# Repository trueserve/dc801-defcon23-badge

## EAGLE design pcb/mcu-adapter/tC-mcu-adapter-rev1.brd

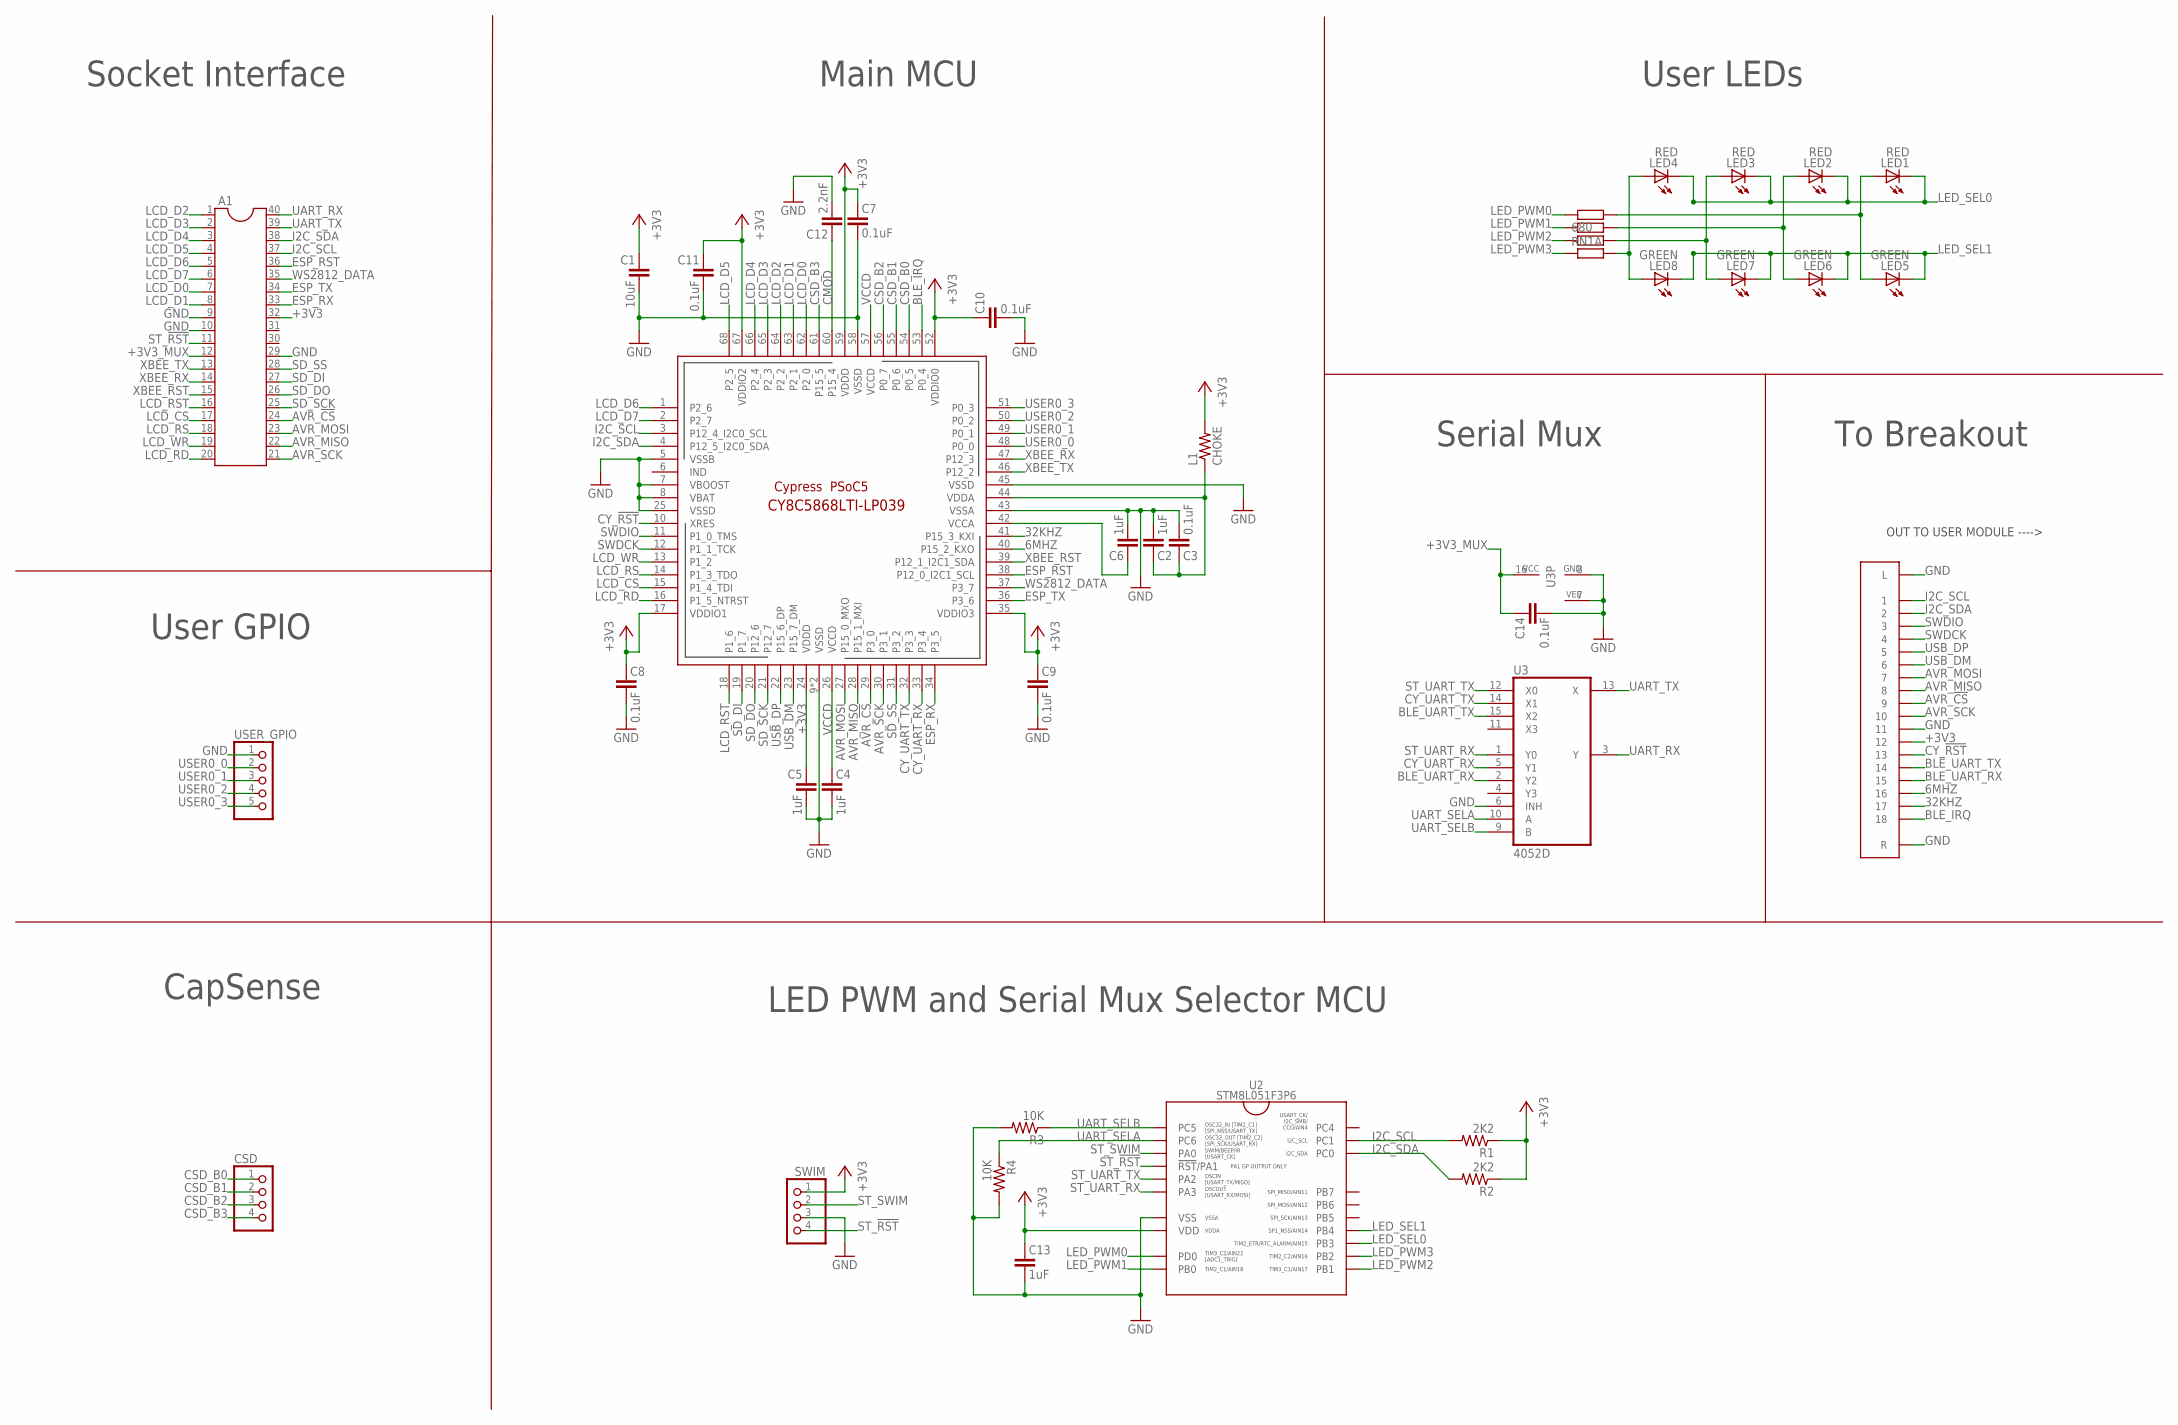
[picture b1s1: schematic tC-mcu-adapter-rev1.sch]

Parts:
A1: DIL40
C1: 10uF; C0805K
C2, C4, C5, C6: 1uF; C0603K
C3, C7, C8, C9, C10, C11: 0.1uF; C0603K
C12: 2.2nF; C0603K
C13: 1uF; C0402K
C14: 0.1uF; C0402K
CN1: FPC_CONN_18PIN_0.5MM_SMT
CSD: CAP_INTERCONNECT
L1: CHOKE; R0805
LED1, LED2, LED3, LED4: RED; LED-805
LED5, LED6, LED7, LED8: GREEN; LED-805
R1, R2: 2K2; R0603
R3, R4: 10K; R0603
RN1: 680; RN8P-4R-CRA06S
SWIM: PINHD-1X4; 1X04
U1: CY8C5XXX-68-N; QFN68N
U2: STM8L051F3P6; TSSOP20
U3: 4052D; SO16
USER_GPIO: PINHD-1X5/90; 1X05/90

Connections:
6MHZ: CN1.16, U1.40 (P15_2_KXO)
32KHZ: CN1.17, U1.41 (P15_3_KXI)
+3V3: A1.32, C1.1, C5.1, C7.1, C8.1, C9.1, C10.1, C11.1, C13.1, CN1.12, L1.2, R1.1, R2.1, SWIM.1, U1.17 (VDDIO1), U1.24 (VDDD), U1.35 (VDDIO3), U1.52 (VDDIO0), U1.59 (VDDD), U1.67 (VDDIO2), U2.8 (VDD)
+3V3_MUX: A1.12, C14.1, U3.16 (VCC)
AVR_!CS: A1.24, CN1.9, U1.29 (P3_0)
AVR_MISO: A1.22, CN1.8, U1.28 (P15_1_MXI)
AVR_MOSI: A1.23, CN1.7, U1.27 (P15_0_MXO)
AVR_SCK: A1.21, CN1.10, U1.30 (P3_1)
BLE_IRQ: CN1.18, U1.53 (P0_4)
BLE_UART_RX: CN1.15, U3.2 (Y2)
BLE_UART_TX: CN1.14, U3.15 (X2)
CMOD: C12.1, U1.60 (P15_4)
CSD_B0: CSD.1, U1.54 (P0_5)
CSD_B1: CSD.2, U1.55 (P0_6)
CSD_B2: CSD.3, U1.56 (P0_7)
CSD_B3: CSD.4, U1.61 (P15_5)
CY_!RST: CN1.13, U1.10 (XRES)
CY_UART_RX: U1.33 (P3_4), U3.5 (Y1)
CY_UART_TX: U1.32 (P3_3), U3.14 (X1)
ESP_RST: A1.36, U1.38 (P12_0_I2C1_SCL)
ESP_RX: A1.33, U1.34 (P3_5)
ESP_TX: A1.34, U1.36 (P3_6)
GND: A1.9, A1.10, A1.29, C1.2, C2.2, C3.2, C4.2, C5.2, C6.2, C7.2, C8.2, C9.2, C10.2, C11.2, C12.2, C13.2, C14.2, CN1.11, CN1.GL (L), CN1.GR (R), R3.2, R4.2, SWIM.3, U1.5 (VSSB), U1.7 (VBOOST), U1.8 (VBAT), U1.9 (VSSD), U1.25 (VSSD), U1.43 (VSSA), U1.45 (VSSD), U1.58 (VSSD), U1.EPAD (VSSD), U2.7 (VSS), U3.6 (INH), U3.7 (VEE), U3.8 (GND), USER_GPIO.1
I2C_SCL: A1.37, CN1.1, R1.2, U1.3 (P12_4_I2C0_SCL), U2.19 (PC1)
I2C_SDA: A1.38, CN1.2, R2.2, U1.4 (P12_5_I2C0_SDA), U2.18 (PC0)
LCD_CS: A1.17, U1.15 (P1_4_TDI)
LCD_D0: A1.7, U1.62 (P2_0)
LCD_D1: A1.8, U1.63 (P2_1)
LCD_D2: A1.1, U1.64 (P2_2)
LCD_D3: A1.2, U1.65 (P2_3)
LCD_D4: A1.3, U1.66 (P2_4)
LCD_D5: A1.4, U1.68 (P2_5)
LCD_D6: A1.5, U1.1 (P2_6)
LCD_D7: A1.6, U1.2 (P2_7)
LCD_RD: A1.20, U1.16 (P1_5_NTRST)
LCD_RS: A1.18, U1.14 (P1_3_TDO)
LCD_RST: A1.16, U1.18 (P1_6)
LCD_WR: A1.19, U1.13 (P1_2)
LED_PWM0: RN1.4 (1), U2.9 (PD0)
LED_PWM0R: LED1.A, LED5.A, RN1.5 (2)
LED_PWM1: RN1.3 (1), U2.10 (PB0)
LED_PWM1R: LED2.A, LED6.A, RN1.6 (2)
LED_PWM2: RN1.2 (1), U2.11 (PB1)
LED_PWM2R: LED3.A, LED7.A, RN1.7 (2)
LED_PWM3: RN1.1, U2.12 (PB2)
LED_PWM3R: LED4.A, LED8.A, RN1.8 (2)
LED_SEL0: LED1.C, LED2.C, LED3.C, LED4.C, U2.13 (PB3)
LED_SEL1: LED5.C, LED6.C, LED7.C, LED8.C, U2.14 (PB4)
SD_DI: A1.27, U1.19 (P1_7)
SD_DO: A1.26, U1.20 (P12_6)
SD_SCK: A1.25, U1.21 (P12_7)
SD_SS: A1.28, U1.31 (P3_2)
ST_!RST: A1.11, SWIM.4, U2.4 (!RST!/PA1)
ST_SWIM: SWIM.2, U2.3 (PA0)
ST_UART_RX: U2.6 (PA3), U3.1 (Y0)
ST_UART_TX: U2.5 (PA2), U3.12 (X0)
SWDCK: CN1.4, U1.12 (P1_1_TCK)
SWDIO: CN1.3, U1.11 (P1_0_TMS)
UART_RX: A1.40, U3.3 (Y)
UART_SELA: R4.1, U2.2 (PC6), U3.10 (A)
UART_SELB: R3.1, U2.1 (PC5), U3.9 (B)
UART_TX: A1.39, U3.13 (X)
USB_DM: CN1.6, U1.23 (P15_7_DM)
USB_DP: CN1.5, U1.22 (P15_6_DP)
USER0_0: U1.48 (P0_0), USER_GPIO.2
USER0_1: U1.49 (P0_1), USER_GPIO.3
USER0_2: U1.50 (P0_2), USER_GPIO.4
USER0_3: U1.51 (P0_3), USER_GPIO.5
VCCA: C6.1, U1.42 (VCCA)
VCCD: C4.1, U1.26 (VCCD), U1.57 (VCCD)
VDDA: C2.1, C3.1, L1.1, U1.44 (VDDA)
WS2812_DATA: A1.35, U1.37 (P3_7)
XBEE_RST: A1.15, U1.39 (P12_1_I2C1_SDA)
XBEE_RX: A1.14, U1.47 (P12_3)
XBEE_TX: A1.13, U1.46 (P12_2)

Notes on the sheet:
OUT TO USER MODULE ---->
Socket Interface
Main MCU
To Breakout
User GPIO
User LEDs
Serial Mux
LED PWM and Serial Mux Selector MCU
CapSense

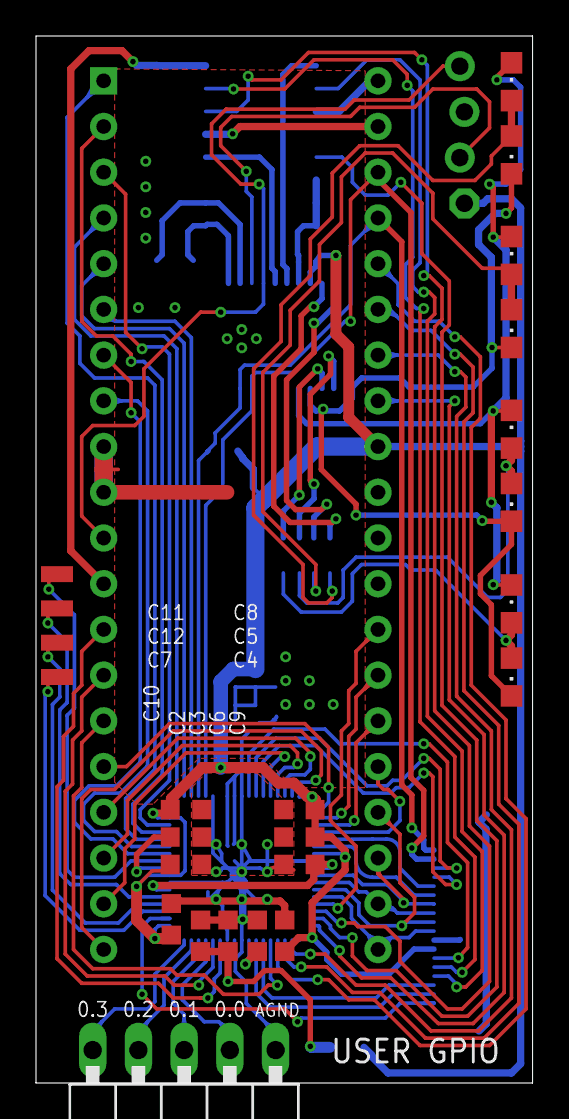
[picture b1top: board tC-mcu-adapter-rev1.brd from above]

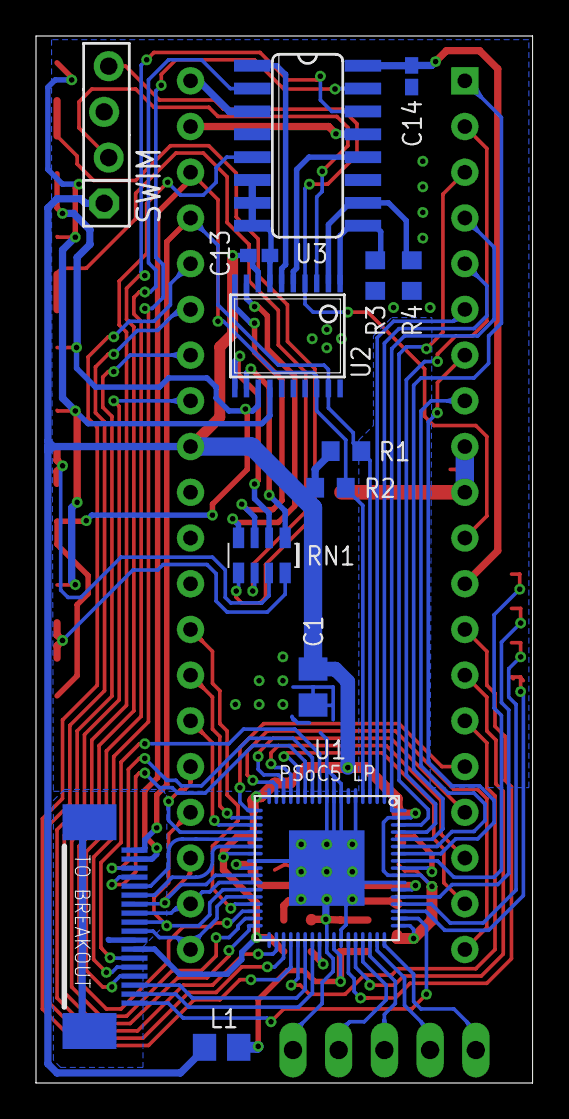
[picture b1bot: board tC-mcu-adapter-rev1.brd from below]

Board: 2 copper layers, 27.6 x 58.2 mm, 36 parts (14 on the bottom side), 75 nets.

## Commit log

2015-10-04 Initial commit of PSoC5 + PSoC4 BLE conversion
    Added PSoC creator project with PSoC pinouts and parts. Added initial
    MCU conversion board schematic, boardfile and gerbers. Added datasheets.
    Added some progress images.
    Moved files around to keep things tidy.
    Updated .gitignore for Eagle and PSoC Creator.
2015-10-04 Renamed Hardware/ to hardware/
2016-02-07 Minor tweaks to MCU adapter board
    - Cleaned up schematic view
    - Finished CapSense breakout pads to second board
    - Changed caps to 0603 to ease hand soldering
    - Minor stuff to silkscreen.

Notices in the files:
parts and their libraries:
PatternAgents-Cypress: License : http://creativecommons.org/licenses/by-sa/3.0
(Creative Commons 3.0)
